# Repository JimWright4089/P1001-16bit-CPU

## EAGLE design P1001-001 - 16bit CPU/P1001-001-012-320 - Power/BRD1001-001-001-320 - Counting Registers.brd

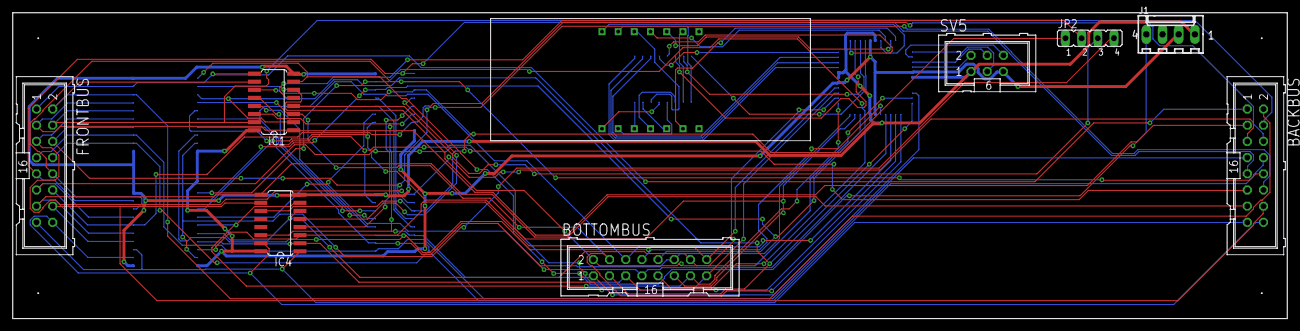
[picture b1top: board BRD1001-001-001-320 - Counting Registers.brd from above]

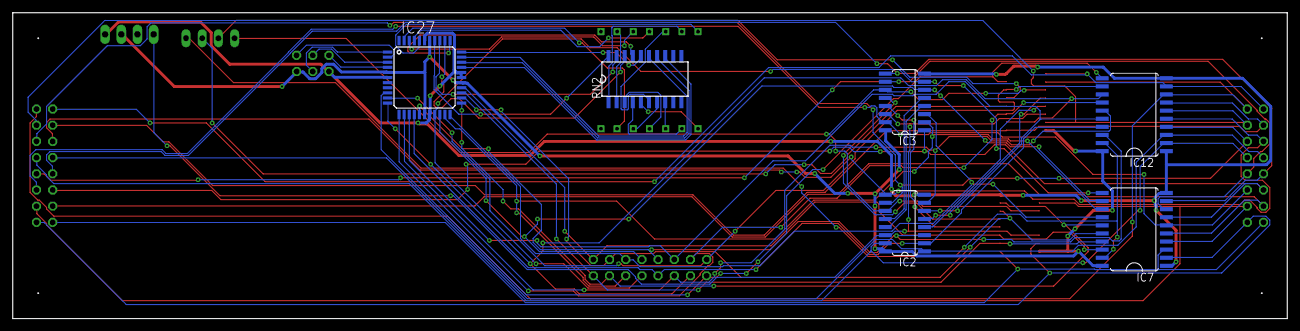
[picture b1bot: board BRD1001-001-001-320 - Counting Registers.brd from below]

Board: 2 copper layers, 200.0 x 48.0 mm, 15 parts (6 on the bottom side), 69 nets.

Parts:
BACKBUS: ML16
BOTTOMBUS: ML16
FRONTBUS: ML16
IC1, IC2, IC3, IC4: 74HC192D; SO16
IC7, IC12: 74AC245DW; SO20W
IC27: MEGA8535-A; TQFP44
J1: 22-27-2041-04; 6410-04
JP2: JP4
RN2: SOMC20
SV5: ML6
U$1: 4-DIGIT-7-SEGMENT

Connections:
!DEC: IC1.4, JP2.3
!INC: IC1.5, JP2.2
!REG_IN: IC1.11, IC2.11, IC3.11, IC4.11, JP2.1
!REG_OUT: IC7.19, IC12.19, JP2.4
A: IC27.37, RN2.20
B: IC27.36, RN2.19
BUS0: BACKBUS.1, FRONTBUS.1, IC1.9, IC12.9
BUS1: BACKBUS.2, FRONTBUS.2, IC1.10, IC12.8
BUS2: BACKBUS.3, FRONTBUS.3, IC1.1, IC12.7
BUS3: BACKBUS.4, FRONTBUS.4, IC1.15, IC12.6
BUS4: BACKBUS.5, FRONTBUS.5, IC2.9, IC12.5
BUS5: BACKBUS.6, FRONTBUS.6, IC2.10, IC12.4
BUS6: BACKBUS.7, FRONTBUS.7, IC2.1, IC12.3
BUS7: BACKBUS.8, FRONTBUS.8, IC2.15, IC12.2
BUS8: BACKBUS.9, FRONTBUS.9, IC3.9, IC7.9
BUS9: BACKBUS.10, FRONTBUS.10, IC3.10, IC7.8
BUS10: BACKBUS.11, FRONTBUS.11, IC3.1, IC7.7
BUS11: BACKBUS.12, FRONTBUS.12, IC3.15, IC7.6
BUS12: BACKBUS.13, FRONTBUS.13, IC4.9, IC7.5
BUS13: BACKBUS.14, FRONTBUS.14, IC4.10, IC7.4
BUS14: BACKBUS.15, FRONTBUS.15, IC4.1, IC7.3
BUS15: BACKBUS.16, FRONTBUS.16, IC4.15, IC7.2
C: IC27.35, RN2.18
CLEAR: IC1.14, IC2.14, IC3.14, IC4.14, J1.4
D: IC27.34, RN2.17
DIG0: IC27.40, U$1.PIN14
DIG1: IC27.41, U$1.PIN11
DIG2: IC27.42, U$1.PIN10
DIG3: IC27.43, U$1.PIN6
DP: IC27.30, RN2.13
E: IC27.33, RN2.16
F: IC27.32, RN2.15
G: IC27.31, RN2.14
GND: IC1.8, IC2.8, IC3.8, IC4.8, IC7.1, IC7.10, IC12.1, IC12.10, IC27.6, IC27.18, IC27.28, IC27.29, IC27.39, J1.1, SV5.1
unnamed: IC1.12, IC2.5
unnamed: IC1.13, IC2.4
unnamed: IC2.12, IC3.5
unnamed: IC2.13, IC3.4
unnamed: IC3.12, IC4.5
unnamed: IC3.13, IC4.4
unnamed: IC27.1, SV5.3
unnamed: IC27.3, SV5.4
unnamed: IC27.2, SV5.6
unnamed: IC27.4, SV5.2
unnamed: RN2.1, U$1.PIN13
unnamed: RN2.2, U$1.PIN9
unnamed: RN2.3, U$1.PIN4
unnamed: RN2.4, U$1.PIN2
unnamed: RN2.5, U$1.PIN1
unnamed: RN2.6, U$1.PIN12
unnamed: RN2.7, U$1.PIN5
unnamed: RN2.8, U$1.PIN3
SIGNAL0: BOTTOMBUS.1, IC1.7, IC12.11, IC27.9
SIGNAL1: BOTTOMBUS.2, IC1.6, IC12.12, IC27.10
SIGNAL2: BOTTOMBUS.3, IC1.2, IC12.13, IC27.11
SIGNAL3: BOTTOMBUS.4, IC1.3, IC12.14, IC27.12
SIGNAL4: BOTTOMBUS.5, IC2.7, IC12.15, IC27.13
SIGNAL5: BOTTOMBUS.6, IC2.6, IC12.16, IC27.14
SIGNAL6: BOTTOMBUS.7, IC2.2, IC12.17, IC27.15
SIGNAL7: BOTTOMBUS.8, IC2.3, IC12.18, IC27.16
SIGNAL8: BOTTOMBUS.9, IC3.7, IC7.11, IC27.19
SIGNAL9: BOTTOMBUS.10, IC3.6, IC7.12, IC27.20
SIGNAL10: BOTTOMBUS.11, IC3.2, IC7.13, IC27.21
SIGNAL11: BOTTOMBUS.12, IC3.3, IC7.14, IC27.22
SIGNAL12: BOTTOMBUS.13, IC4.7, IC7.15, IC27.23
SIGNAL13: BOTTOMBUS.14, IC4.6, IC7.16, IC27.24
SIGNAL14: BOTTOMBUS.15, IC4.2, IC7.17, IC27.25
SIGNAL15: BOTTOMBUS.16, IC4.3, IC7.18, IC27.26
VCC: IC1.16, IC2.16, IC3.16, IC4.16, IC7.20, IC12.20, IC27.5, IC27.17, IC27.27, IC27.38, J1.2, SV5.5

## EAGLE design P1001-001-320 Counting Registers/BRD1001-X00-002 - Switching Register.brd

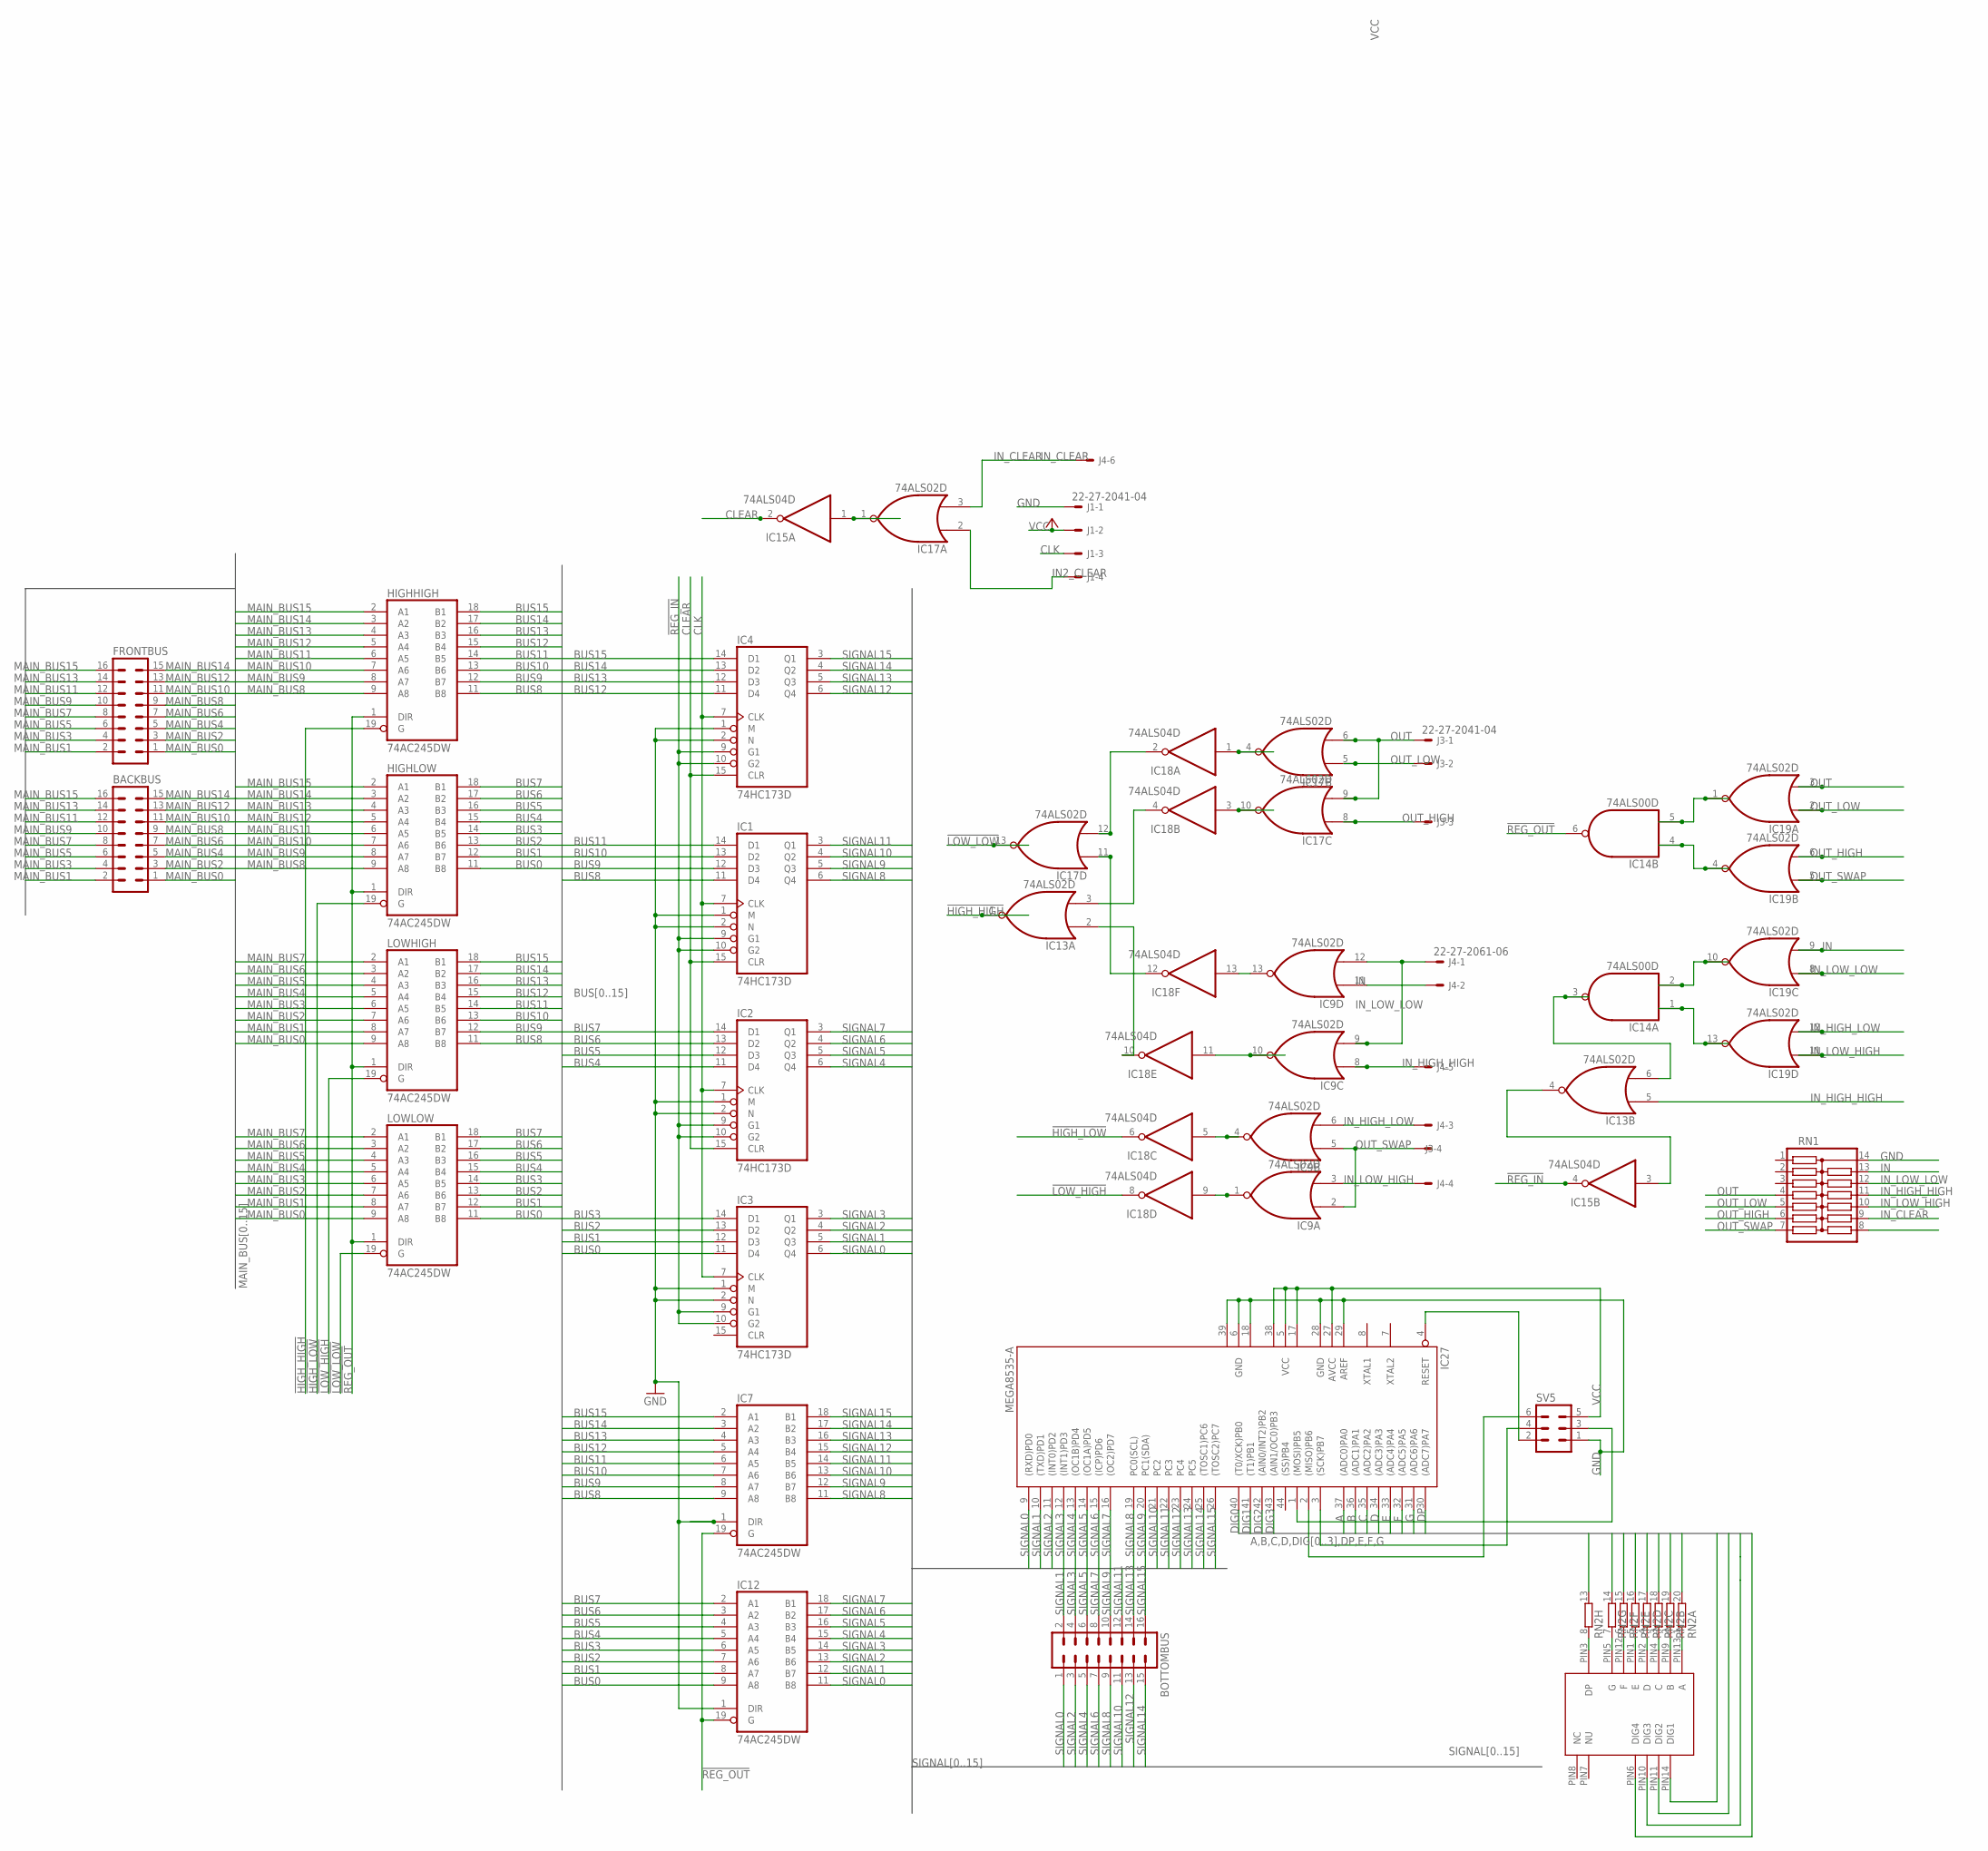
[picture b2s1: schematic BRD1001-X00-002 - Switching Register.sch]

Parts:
BACKBUS: ML16
BOTTOMBUS: ML16
FRONTBUS: ML16
HIGHHIGH: 74AC245DW; SO20W
HIGHLOW: 74AC245DW; SO20W
IC1, IC2, IC3, IC4: 74HC173D; SO16
IC7, IC12: 74AC245DW; SO20W
IC9, IC13, IC17, IC19: 74ALS02D; SO14
IC14: 74ALS00D; SO14
IC15, IC18: 74ALS04D; SO14
IC27: MEGA8535-A; TQFP44
J1, J3: 22-27-2041-04; 6410-04
J4: 22-27-2061-06; 6410-06
LOWHIGH: 74AC245DW; SO20W
LOWLOW: 74AC245DW; SO20W
RN1: 13RSOMC; SOMC14
RN2: 10R-NSOMC; SOMC20
SV5: ML6
U$1: 4-DIGIT-7-SEGMENT

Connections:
!HIGH_HIGH: HIGHHIGH.19 (G), IC13.1 (O)
!HIGH_LOW: HIGHLOW.19 (G), IC18.6 (O)
!LOW_HIGH: IC18.8 (O), LOWHIGH.19 (G)
!LOW_LOW: IC17.13 (O), LOWLOW.19 (G)
!REG_IN: IC1.9 (G1), IC1.10 (G2), IC2.9 (G1), IC2.10 (G2), IC3.9 (G1), IC3.10 (G2), IC4.9 (G1), IC4.10 (G2), IC15.4 (O)
!REG_OUT: HIGHHIGH.1 (DIR), HIGHLOW.1 (DIR), IC7.19 (G), IC12.19 (G), IC14.6 (O), LOWHIGH.1 (DIR), LOWLOW.1 (DIR)
A: IC27.37 ((ADC0)PA0), RN2.20 (2)
B: IC27.36 ((ADC1)PA1), RN2.19 (2)
BUS0: HIGHLOW.11 (B8), IC3.11 (D4), IC12.9 (A8), LOWLOW.11 (B8)
BUS1: HIGHLOW.12 (B7), IC3.12 (D3), IC12.8 (A7), LOWLOW.12 (B7)
BUS2: HIGHLOW.13 (B6), IC3.13 (D2), IC12.7 (A6), LOWLOW.13 (B6)
BUS3: HIGHLOW.14 (B5), IC3.14 (D1), IC12.6 (A5), LOWLOW.14 (B5)
BUS4: HIGHLOW.15 (B4), IC2.11 (D4), IC12.5 (A4), LOWLOW.15 (B4)
BUS5: HIGHLOW.16 (B3), IC2.12 (D3), IC12.4 (A3), LOWLOW.16 (B3)
BUS6: HIGHLOW.17 (B2), IC2.13 (D2), IC12.3 (A2), LOWLOW.17 (B2)
BUS7: HIGHLOW.18 (B1), IC2.14 (D1), IC12.2 (A1), LOWLOW.18 (B1)
BUS8: HIGHHIGH.11 (B8), IC1.11 (D4), IC7.9 (A8), LOWHIGH.11 (B8)
BUS9: HIGHHIGH.12 (B7), IC1.12 (D3), IC7.8 (A7), LOWHIGH.12 (B7)
BUS10: HIGHHIGH.13 (B6), IC1.13 (D2), IC7.7 (A6), LOWHIGH.13 (B6)
BUS11: HIGHHIGH.14 (B5), IC1.14 (D1), IC7.6 (A5), LOWHIGH.14 (B5)
BUS12: HIGHHIGH.15 (B4), IC4.11 (D4), IC7.5 (A4), LOWHIGH.15 (B4)
BUS13: HIGHHIGH.16 (B3), IC4.12 (D3), IC7.4 (A3), LOWHIGH.16 (B3)
BUS14: HIGHHIGH.17 (B2), IC4.13 (D2), IC7.3 (A2), LOWHIGH.17 (B2)
BUS15: HIGHHIGH.18 (B1), IC4.14 (D1), IC7.2 (A1), LOWHIGH.18 (B1)
C: IC27.35 ((ADC2)PA2), RN2.18 (2)
CLEAR: IC1.15 (CLR), IC2.15 (CLR), IC4.15 (CLR), IC15.2 (O)
CLK: IC1.7 (CLK), IC2.7 (CLK), IC3.7 (CLK), IC4.7 (CLK), J1.3
D: IC27.34 ((ADC3)PA3), RN2.17 (2)
DIG0: IC27.40 ((T0/XCK)PB0), U$1.PIN14 (DIG1)
DIG1: IC27.41 ((T1)PB1), U$1.PIN11 (DIG2)
DIG2: IC27.42 ((AIN0/INT2)PB2), U$1.PIN10 (DIG3)
DIG3: IC27.43 ((AIN1/OC0)PB3), U$1.PIN6 (DIG4)
DP: IC27.30 ((ADC7)PA7), RN2.13 (2)
E: IC27.33 ((ADC4)PA4), RN2.16 (2)
F: IC27.32 ((ADC5)PA5), RN2.15 (2)
G: IC27.31 ((ADC6)PA6), RN2.14 (2)
GND: HIGHHIGH.10 (GND), HIGHLOW.10 (GND), IC1.1 (M), IC1.2 (N), IC1.8 (GND), IC2.1 (M), IC2.2 (N), IC2.8 (GND), IC3.1 (M), IC3.2 (N), IC3.8 (GND), IC4.1 (M), IC4.2 (N), IC4.8 (GND), IC7.1 (DIR), IC7.10 (GND), IC9.7 (GND), IC12.1 (DIR), IC12.10 (GND), IC13.7 (GND), IC14.7 (GND), IC15.7 (GND), IC17.7 (GND), IC18.7 (GND), IC19.7 (GND), IC27.6 (GND), IC27.18 (GND1), IC27.28 (GND), IC27.29 (AREF), IC27.39 (GND2), J1.1, LOWHIGH.10 (GND), LOWLOW.10 (GND), RN1.14, SV5.1
IN: IC9.9 (I1), IC9.12 (I1), IC19.9 (I1), J4.1, RN1.13
IN2_CLEAR: IC17.2 (I0), J1.4
IN_CLEAR: IC17.3 (I1), J4.6, RN1.9
IN_HIGH_HIGH: IC9.8 (I0), IC13.5 (I0), J4.5, RN1.11
IN_HIGH_LOW: IC9.6 (I1), IC19.12 (I1), J4.3
IN_LOW_HIGH: IC9.3 (I1), IC19.11 (I0), J4.4, RN1.10
IN_LOW_LOW: IC9.11 (I0), IC19.8 (I0), J4.2, RN1.12
MAIN_BUS0: BACKBUS.1, FRONTBUS.1, LOWHIGH.9 (A8), LOWLOW.9 (A8)
MAIN_BUS1: BACKBUS.2, FRONTBUS.2, LOWHIGH.8 (A7), LOWLOW.8 (A7)
MAIN_BUS2: BACKBUS.3, FRONTBUS.3, LOWHIGH.7 (A6), LOWLOW.7 (A6)
MAIN_BUS3: BACKBUS.4, FRONTBUS.4, LOWHIGH.6 (A5), LOWLOW.6 (A5)
MAIN_BUS4: BACKBUS.5, FRONTBUS.5, LOWHIGH.5 (A4), LOWLOW.5 (A4)
MAIN_BUS5: BACKBUS.6, FRONTBUS.6, LOWHIGH.4 (A3), LOWLOW.4 (A3)
MAIN_BUS6: BACKBUS.7, FRONTBUS.7, LOWHIGH.3 (A2), LOWLOW.3 (A2)
MAIN_BUS7: BACKBUS.8, FRONTBUS.8, LOWHIGH.2 (A1), LOWLOW.2 (A1)
MAIN_BUS8: BACKBUS.9, FRONTBUS.9, HIGHHIGH.9 (A8), HIGHLOW.9 (A8)
MAIN_BUS9: BACKBUS.10, FRONTBUS.10, HIGHHIGH.8 (A7), HIGHLOW.8 (A7)
MAIN_BUS10: BACKBUS.11, FRONTBUS.11, HIGHHIGH.7 (A6), HIGHLOW.7 (A6)
MAIN_BUS11: BACKBUS.12, FRONTBUS.12, HIGHHIGH.6 (A5), HIGHLOW.6 (A5)
MAIN_BUS12: BACKBUS.13, FRONTBUS.13, HIGHHIGH.5 (A4), HIGHLOW.5 (A4)
MAIN_BUS13: BACKBUS.14, FRONTBUS.14, HIGHHIGH.4 (A3), HIGHLOW.4 (A3)
MAIN_BUS14: BACKBUS.15, FRONTBUS.15, HIGHHIGH.3 (A2), HIGHLOW.3 (A2)
MAIN_BUS15: BACKBUS.16, FRONTBUS.16, HIGHHIGH.2 (A1), HIGHLOW.2 (A1)
unnamed: IC17.4 (O), IC18.1 (I)
unnamed: IC17.10 (O), IC18.3 (I)
unnamed: IC14.2 (I1), IC19.10 (O)
unnamed: IC14.1 (I0), IC19.13 (O)
unnamed: IC15.1 (I), IC17.1 (O)
unnamed: IC9.13 (O), IC18.13 (I)
unnamed: IC14.5 (I1), IC19.1 (O)
unnamed: IC14.4 (I0), IC19.4 (O)
unnamed: IC9.10 (O), IC18.11 (I)
unnamed: IC17.12 (I1), IC18.2 (O)
unnamed: IC17.11 (I0), IC18.12 (O)
unnamed: IC13.3 (I1), IC18.4 (O)
unnamed: IC13.2 (I0), IC18.10 (O)
unnamed: IC9.4 (O), IC18.5 (I)
unnamed: IC9.1 (O), IC18.9 (I)
unnamed: IC13.6 (I1), IC14.3 (O)
unnamed: IC13.4 (O), IC15.3 (I)
unnamed: IC27.1 ((MOSI)PB5), SV5.3
unnamed: IC27.3 ((SCK)PB7), SV5.4
unnamed: IC27.2 ((MISO)PB6), SV5.6
unnamed: IC27.4 (RESET), SV5.2
unnamed: RN2.1, U$1.PIN13 (A)
unnamed: RN2.2 (1), U$1.PIN9 (B)
unnamed: RN2.3 (1), U$1.PIN4 (C)
unnamed: RN2.4 (1), U$1.PIN2 (D)
unnamed: RN2.5 (1), U$1.PIN1 (E)
unnamed: RN2.6 (1), U$1.PIN12 (F)
unnamed: RN2.7 (1), U$1.PIN5 (G)
unnamed: RN2.8 (1), U$1.PIN3 (DP)
OUT: IC17.6 (I1), IC17.9 (I1), IC19.3 (I1), J3.1, RN1.4
OUT_HIGH: IC17.8 (I0), IC19.6 (I1), J3.3, RN1.6
OUT_LOW: IC17.5 (I0), IC19.2 (I0), J3.2, RN1.5
OUT_SWAP: IC9.2 (I0), IC9.5 (I0), IC19.5 (I0), J3.4, RN1.7
SIGNAL0: BOTTOMBUS.1, IC3.6 (Q4), IC12.11 (B8), IC27.9 ((RXD)PD0)
SIGNAL1: BOTTOMBUS.2, IC3.5 (Q3), IC12.12 (B7), IC27.10 ((TXD)PD1)
SIGNAL2: BOTTOMBUS.3, IC3.4 (Q2), IC12.13 (B6), IC27.11 ((INT0)PD2)
SIGNAL3: BOTTOMBUS.4, IC3.3 (Q1), IC12.14 (B5), IC27.12 ((INT1)PD3)
SIGNAL4: BOTTOMBUS.5, IC2.6 (Q4), IC12.15 (B4), IC27.13 ((OC1B)PD4)
SIGNAL5: BOTTOMBUS.6, IC2.5 (Q3), IC12.16 (B3), IC27.14 ((OC1A)PD5)
SIGNAL6: BOTTOMBUS.7, IC2.4 (Q2), IC12.17 (B2), IC27.15 ((ICP)PD6)
SIGNAL7: BOTTOMBUS.8, IC2.3 (Q1), IC12.18 (B1), IC27.16 ((OC2)PD7)
SIGNAL8: BOTTOMBUS.9, IC1.6 (Q4), IC7.11 (B8), IC27.19 (PC0(SCL))
SIGNAL9: BOTTOMBUS.10, IC1.5 (Q3), IC7.12 (B7), IC27.20 (PC1(SDA))
SIGNAL10: BOTTOMBUS.11, IC1.4 (Q2), IC7.13 (B6), IC27.21 (PC2)
SIGNAL11: BOTTOMBUS.12, IC1.3 (Q1), IC7.14 (B5), IC27.22 (PC3)
SIGNAL12: BOTTOMBUS.13, IC4.6 (Q4), IC7.15 (B4), IC27.23 (PC4)
SIGNAL13: BOTTOMBUS.14, IC4.5 (Q3), IC7.16 (B3), IC27.24 (PC5)
SIGNAL14: BOTTOMBUS.15, IC4.4 (Q2), IC7.17 (B2), IC27.25 ((TOSC1)PC6)
SIGNAL15: BOTTOMBUS.16, IC4.3 (Q1), IC7.18 (B1), IC27.26 ((TOSC2)PC7)
VCC: HIGHHIGH.20 (VCC), HIGHLOW.20 (VCC), IC1.16 (VCC), IC2.16 (VCC), IC3.16 (VCC), IC4.16 (VCC), IC7.20 (VCC), IC9.14 (VCC), IC12.20 (VCC), IC13.14 (VCC), IC14.14 (VCC), IC15.14 (VCC), IC17.14 (VCC), IC18.14 (VCC), IC19.14 (VCC), IC27.5 (VCC), IC27.17 (VCC1), IC27.27 (AVCC), IC27.38 (VCC2), J1.2, LOWHIGH.20 (VCC), LOWLOW.20 (VCC), SV5.5

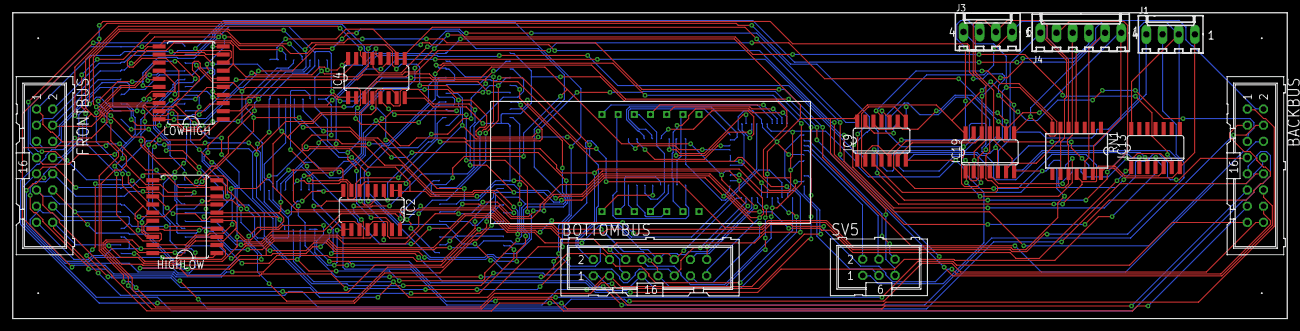
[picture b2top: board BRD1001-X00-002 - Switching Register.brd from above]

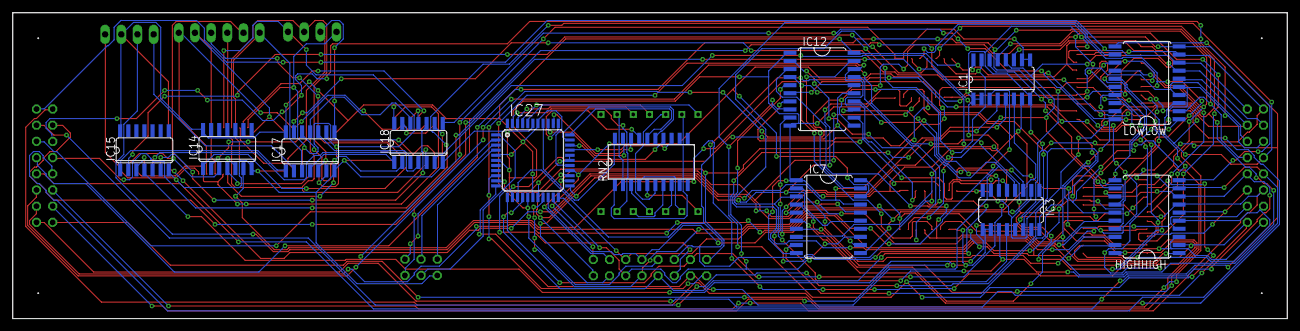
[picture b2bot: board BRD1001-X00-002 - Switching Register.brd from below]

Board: 2 copper layers, 200.0 x 48.0 mm, 28 parts (12 on the bottom side), 110 nets.

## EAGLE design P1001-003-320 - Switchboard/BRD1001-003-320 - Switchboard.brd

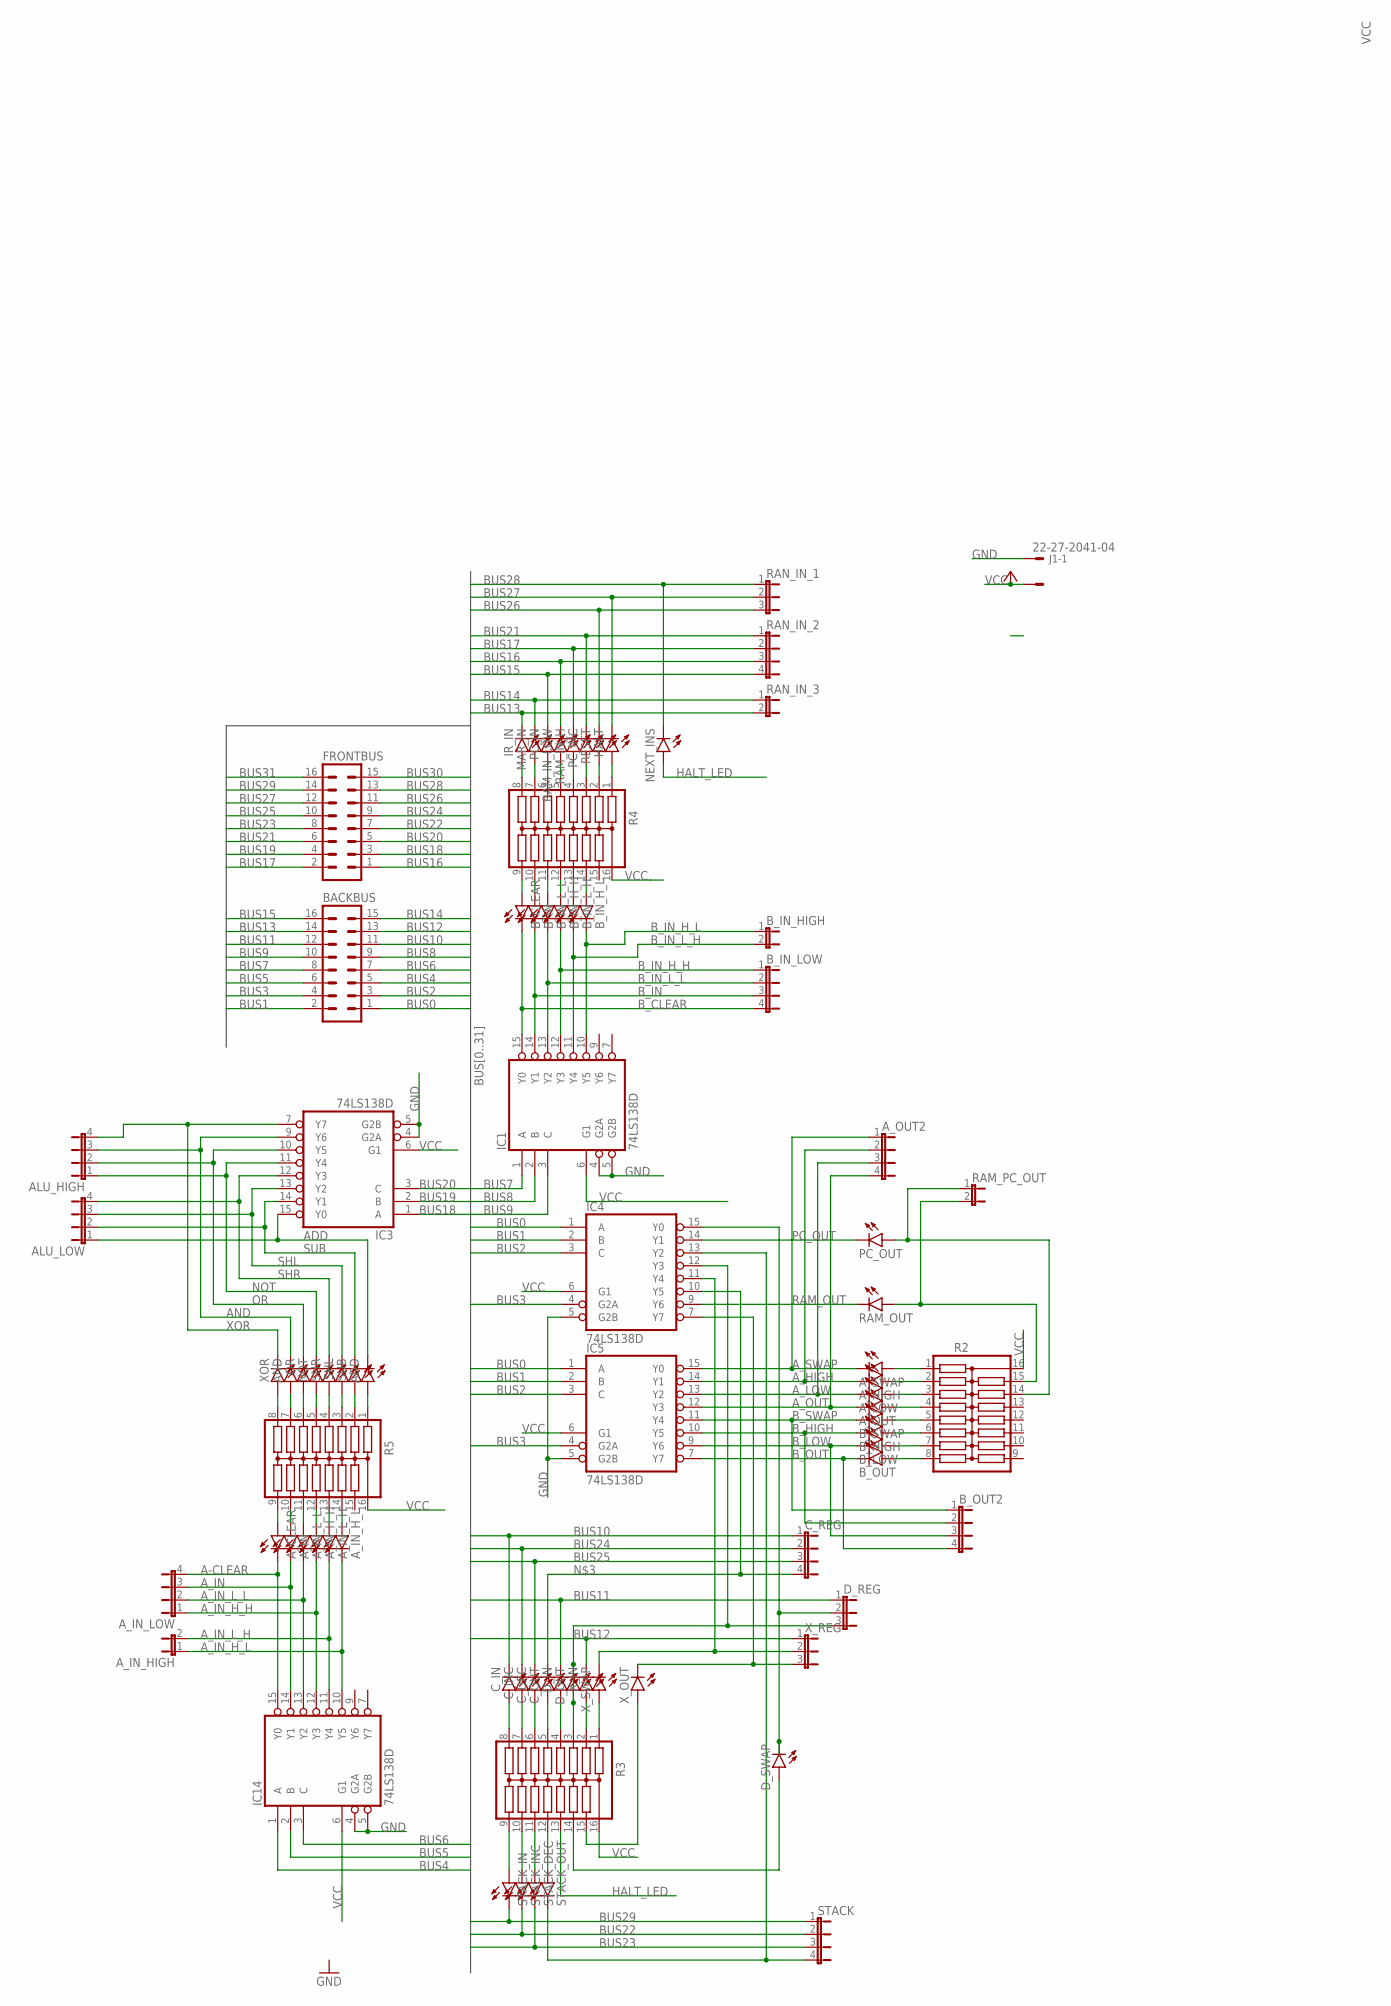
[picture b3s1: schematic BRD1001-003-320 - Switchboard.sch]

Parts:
ADD: LEDSFH482; SFH482
ALU_HIGH: JP4E; JP4
ALU_LOW: JP4E; JP4
AND: LEDSFH482; SFH482
A_CLEAR: LEDSFH482; SFH482
A_HIGH: LEDSFH482; SFH482
A_IN: LEDSFH482; SFH482
A_IN_HIGH: JP1E; JP1
A_IN_H_H: LEDSFH482; SFH482
A_IN_H_L: LEDSFH482; SFH482
A_IN_LOW: JP4E; JP4
A_IN_L_H: LEDSFH482; SFH482
A_IN_L_L: LEDSFH482; SFH482
A_LOW: LEDSFH482; SFH482
A_OUT: LEDSFH482; SFH482
A_OUT2: JP4E; JP4
A_SWAP: LEDSFH482; SFH482
BACKBUS: ML16
B_CLEAR: LEDSFH482; SFH482
B_HIGH: LEDSFH482; SFH482
B_IN: LEDSFH482; SFH482
B_IN_HIGH: JP1E; JP1
B_IN_H_H: LEDSFH482; SFH482
B_IN_H_L: LEDSFH482; SFH482
B_IN_LOW: JP4E; JP4
B_IN_L_H: LEDSFH482; SFH482
B_IN_L_L: LEDSFH482; SFH482
B_LOW: LEDSFH482; SFH482
B_OUT: LEDSFH482; SFH482
B_OUT2: JP4E; JP4
B_SWAP: LEDSFH482; SFH482
C_DEC: LEDSFH482; SFH482
C_IN: LEDSFH482; SFH482
C_INC: LEDSFH482; SFH482
C_OUT: LEDSFH482; SFH482
C_REG: JP4E; JP4
D_IN: LEDSFH482; SFH482
D_OUT: LEDSFH482; SFH482
D_REG: JP2W
D_SWAP: LEDSFH482; SFH482
FRONTBUS: ML16
HALT: LEDSFH482; SFH482
IC1, IC3, IC4, IC5, IC14: 74LS138D; SO16
IR_IN: LEDSFH482; SFH482
J1: 22-27-2041-04; 6410-04
MAR_IN: LEDSFH482; SFH482
NEXT_INS: LEDSFH482; SFH482
NOT: LEDSFH482; SFH482
OR: LEDSFH482; SFH482
PC_IN: LEDSFH482; SFH482
PC_INC: LEDSFH482; SFH482
PC_OUT: LEDSFH482; SFH482
R2, R3, R4, R5: 2NBS16-15; SO16
RAM_IN_H: LEDSFH482; SFH482
RAM_IN_LOW: LEDSFH482; SFH482
RAM_OUT: LEDSFH482; SFH482
RAM_PC_OUT: JP1E; JP1
RAN_IN_1: JP2W
RAN_IN_2: JP4E; JP4
RAN_IN_3: JP1E; JP1
RESET: LEDSFH482; SFH482
SHL: LEDSFH482; SFH482
SHR: LEDSFH482; SFH482
STACK: JP4E; JP4
STACK_DEC: LEDSFH482; SFH482
STACK_IN: LEDSFH482; SFH482
STACK_INC: LEDSFH482; SFH482
STACK_OUT: LEDSFH482; SFH482
SUB: LEDSFH482; SFH482
XOR: LEDSFH482; SFH482
X_IN: LEDSFH482; SFH482
X_OUT: LEDSFH482; SFH482
X_REG: JP2W
X_SWAP: LEDSFH482; SFH482

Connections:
A-CLEAR: A_CLEAR.K (C), A_IN_LOW.4, IC14.15 (Y0)
ADD: ADD.K (C), ALU_LOW.1, IC3.15 (Y0)
AND: ALU_HIGH.3, AND.K (C), IC3.9 (Y6)
A_HIGH: A_HIGH.K (C), A_OUT2.2, IC5.14 (Y1)
A_IN: A_IN.K (C), A_IN_LOW.3, IC14.14 (Y1)
A_IN_H_H: A_IN_H_H.K (C), A_IN_LOW.1, IC14.12 (Y3)
A_IN_H_L: A_IN_HIGH.1, A_IN_H_L.K (C), IC14.10 (Y5)
A_IN_L_H: A_IN_HIGH.2, A_IN_L_H.K (C), IC14.11 (Y4)
A_IN_L_L: A_IN_LOW.2, A_IN_L_L.K (C), IC14.13 (Y2)
A_LOW: A_LOW.K (C), A_OUT2.3, IC5.13 (Y2)
A_OUT: A_OUT.K (C), A_OUT2.4, IC5.12 (Y3)
A_SWAP: A_OUT2.1, A_SWAP.K (C), IC5.15 (Y0)
BUS0: BACKBUS.1, IC4.1 (A), IC5.1 (A)
BUS1: BACKBUS.2, IC4.2 (B), IC5.2 (B)
BUS2: BACKBUS.3, IC4.3 (C), IC5.3 (C)
BUS3: BACKBUS.4, IC4.4 (G2A), IC5.4 (G2A)
BUS4: BACKBUS.5, IC14.1 (A)
BUS5: BACKBUS.6, IC14.2 (B)
BUS6: BACKBUS.7, IC14.3 (C)
BUS7: BACKBUS.8, IC1.1 (A)
BUS8: BACKBUS.9, IC1.2 (B)
BUS9: BACKBUS.10, IC1.3 (C)
BUS10: BACKBUS.11, C_IN.K (C), C_REG.1
BUS11: BACKBUS.12, D_IN.K (C), D_REG.1
BUS12: BACKBUS.13, X_IN.K (C), X_REG.1
BUS13: BACKBUS.14, IR_IN.K (C), RAN_IN_3.2
BUS14: BACKBUS.15, MAR_IN.K (C), RAN_IN_3.1
BUS15: BACKBUS.16, PC_IN.K (C), RAN_IN_2.4
BUS16: FRONTBUS.1, RAM_IN_LOW.K (C), RAN_IN_2.3
BUS17: FRONTBUS.2, RAM_IN_H.K (C), RAN_IN_2.2
BUS18: FRONTBUS.3, IC3.1 (A)
BUS19: FRONTBUS.4, IC3.2 (B)
BUS20: FRONTBUS.5, IC3.3 (C)
BUS21: FRONTBUS.6, PC_INC.K (C), RAN_IN_2.1
BUS22: FRONTBUS.7, STACK.2, STACK_INC.K (C)
BUS23: FRONTBUS.8, STACK.3, STACK_DEC.K (C)
BUS24: C_INC.K (C), C_REG.2, FRONTBUS.9
BUS25: C_DEC.K (C), C_REG.3, FRONTBUS.10
BUS26: FRONTBUS.11, RAN_IN_1.3, RESET.K (C)
BUS27: FRONTBUS.12, HALT.K (C), RAN_IN_1.2
BUS28: FRONTBUS.13, NEXT_INS.K (C), RAN_IN_1.1
BUS29: FRONTBUS.14, STACK.1, STACK_IN.K (C)
BUS30: FRONTBUS.15
BUS31: FRONTBUS.16
B_CLEAR: B_CLEAR.K (C), B_IN_LOW.4, IC1.15 (Y0)
B_HIGH: B_HIGH.K (C), B_OUT2.2, IC5.10 (Y5)
B_IN: B_IN.K (C), B_IN_LOW.3, IC1.14 (Y1)
B_IN_H_H: B_IN_H_H.K (C), B_IN_LOW.1, IC1.12 (Y3)
B_IN_H_L: B_IN_HIGH.1, B_IN_H_L.K (C), IC1.10 (Y5)
B_IN_L_H: B_IN_HIGH.2, B_IN_L_H.K (C), IC1.11 (Y4)
B_IN_L_L: B_IN_LOW.2, B_IN_L_L.K (C), IC1.13 (Y2)
B_LOW: B_LOW.K (C), B_OUT2.3, IC5.9 (Y6)
B_OUT: B_OUT.K (C), B_OUT2.4, IC5.7 (Y7)
B_SWAP: B_OUT2.1, B_SWAP.K (C), IC5.11 (Y4)
GND: IC1.4 (G2A), IC1.5 (G2B), IC1.8 (GND), IC3.4 (G2A), IC3.5 (G2B), IC3.8 (GND), IC4.5 (G2B), IC4.8 (GND), IC5.5 (G2B), IC5.8 (GND), IC14.4 (G2A), IC14.5 (G2B), IC14.8 (GND), J1.1
HALT_LED: NEXT_INS.A, R3.13
unnamed: C_IN.A, R3.8
unnamed: C_OUT.K (C), C_REG.4, IC4.10 (Y5)
unnamed: C_OUT.A, R3.5
unnamed: C_DEC.A, R3.6
unnamed: C_INC.A, R3.7
unnamed: D_OUT.A, D_OUT.K (C), D_REG.3, IC4.12 (Y3), R3.3
unnamed: D_IN.A, R3.4
unnamed: R3.1, X_SWAP.A
unnamed: IC4.11 (Y4), X_REG.2, X_SWAP.K (C)
unnamed: R3.2, X_IN.A
unnamed: IC4.7 (Y7), X_OUT.K (C), X_REG.3
unnamed: R3.15, X_OUT.A
unnamed: R3.9, STACK_IN.A
unnamed: R3.10, STACK_INC.A
unnamed: R3.11, STACK_DEC.A
unnamed: R3.12, STACK_OUT.A
unnamed: IC4.13 (Y2), STACK.4, STACK_OUT.K (C)
unnamed: D_REG.2, D_SWAP.K (C), IC4.15 (Y0)
unnamed: D_SWAP.A, R3.14
unnamed: A_CLEAR.A, R5.9
unnamed: ADD.A, R5.1
unnamed: A_IN.A, R5.10
unnamed: B_CLEAR.A, R4.9
unnamed: B_IN.A, R4.10
unnamed: B_IN_L_L.A, R4.11
unnamed: B_IN_H_H.A, R4.12
unnamed: R5.8, XOR.A
unnamed: AND.A, R5.7
unnamed: OR.A, R5.6
unnamed: NOT.A, R5.5
unnamed: R5.4, SHR.A
unnamed: R5.3, SHL.A
unnamed: R5.2, SUB.A
unnamed: B_IN_L_H.A, R4.13
unnamed: B_IN_H_L.A, R4.14
unnamed: A_IN_L_L.A, R5.11
unnamed: A_IN_H_H.A, R5.12
unnamed: A_IN_L_H.A, R5.13
unnamed: A_IN_H_L.A, R5.14
unnamed: R2.15, RAM_OUT.A, RAM_PC_OUT.2
unnamed: A_SWAP.A, R2.1
unnamed: A_HIGH.A, R2.2
unnamed: A_LOW.A, R2.3
unnamed: A_OUT.A, R2.4
unnamed: B_SWAP.A, R2.5
unnamed: B_HIGH.A, R2.6
unnamed: B_LOW.A, R2.7
unnamed: B_OUT.A, R2.8
unnamed: PC_OUT.A, R2.14, RAM_PC_OUT.1
unnamed: IR_IN.A, R4.8
unnamed: MAR_IN.A, R4.7
unnamed: PC_IN.A, R4.6
unnamed: R4.5, RAM_IN_LOW.A
unnamed: R4.4, RAM_IN_H.A
unnamed: PC_INC.A, R4.3
unnamed: R4.2, RESET.A
unnamed: HALT.A, R4.1
NOT: ALU_HIGH.1, IC3.11 (Y4), NOT.K (C)
OR: ALU_HIGH.2, IC3.10 (Y5), OR.K (C)
PC_OUT: IC4.14 (Y1), PC_OUT.K (C)
RAM_OUT: IC4.9 (Y6), RAM_OUT.K (C)
SHL: ALU_LOW.3, IC3.13 (Y2), SHL.K (C)
SHR: ALU_LOW.4, IC3.12 (Y3), SHR.K (C)
SUB: ALU_LOW.2, IC3.14 (Y1), SUB.K (C)
VCC: IC1.6 (G1), IC1.16 (VCC), IC3.6 (G1), IC3.16 (VCC), IC4.6 (G1), IC4.16 (VCC), IC5.6 (G1), IC5.16 (VCC), IC14.6 (G1), IC14.16 (VCC), J1.2, R2.16, R3.16, R4.16, R5.16
XOR: ALU_HIGH.4, IC3.7 (Y7), XOR.K (C)

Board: 2 copper layers, 81 parts (7 on the bottom side), 120 nets, no tracks yet.
